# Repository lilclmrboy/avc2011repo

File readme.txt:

##########################################################################
# Readme.txt file for AVG2011 project

Download Acroname product sources and integrate the SVN repository. 
Aka, how do I get these files to just work with the download files. 
Launch a terminal session and get to it. 

1.) Move into a directory that you just downloaded the files from Acroname.
2.) Copy the files into your avc2011repo directory

$ cp -Rv acroname/ /Users/you/avc2011rep/source

That should be it. Get working!

##########################################################################
# TEAWare information
# Getting the Stem files ready for deployment to the Stem network

There is a make command to build the project settings for the stem network.

$ make dump

This should create a file to load all the TEAWare onto the Stem network. From the aConsole application:

brainstem> braindump avc2011_dump.dump
wtf

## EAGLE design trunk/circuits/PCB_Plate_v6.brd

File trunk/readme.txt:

# Readme.txt file for AVG2011 project

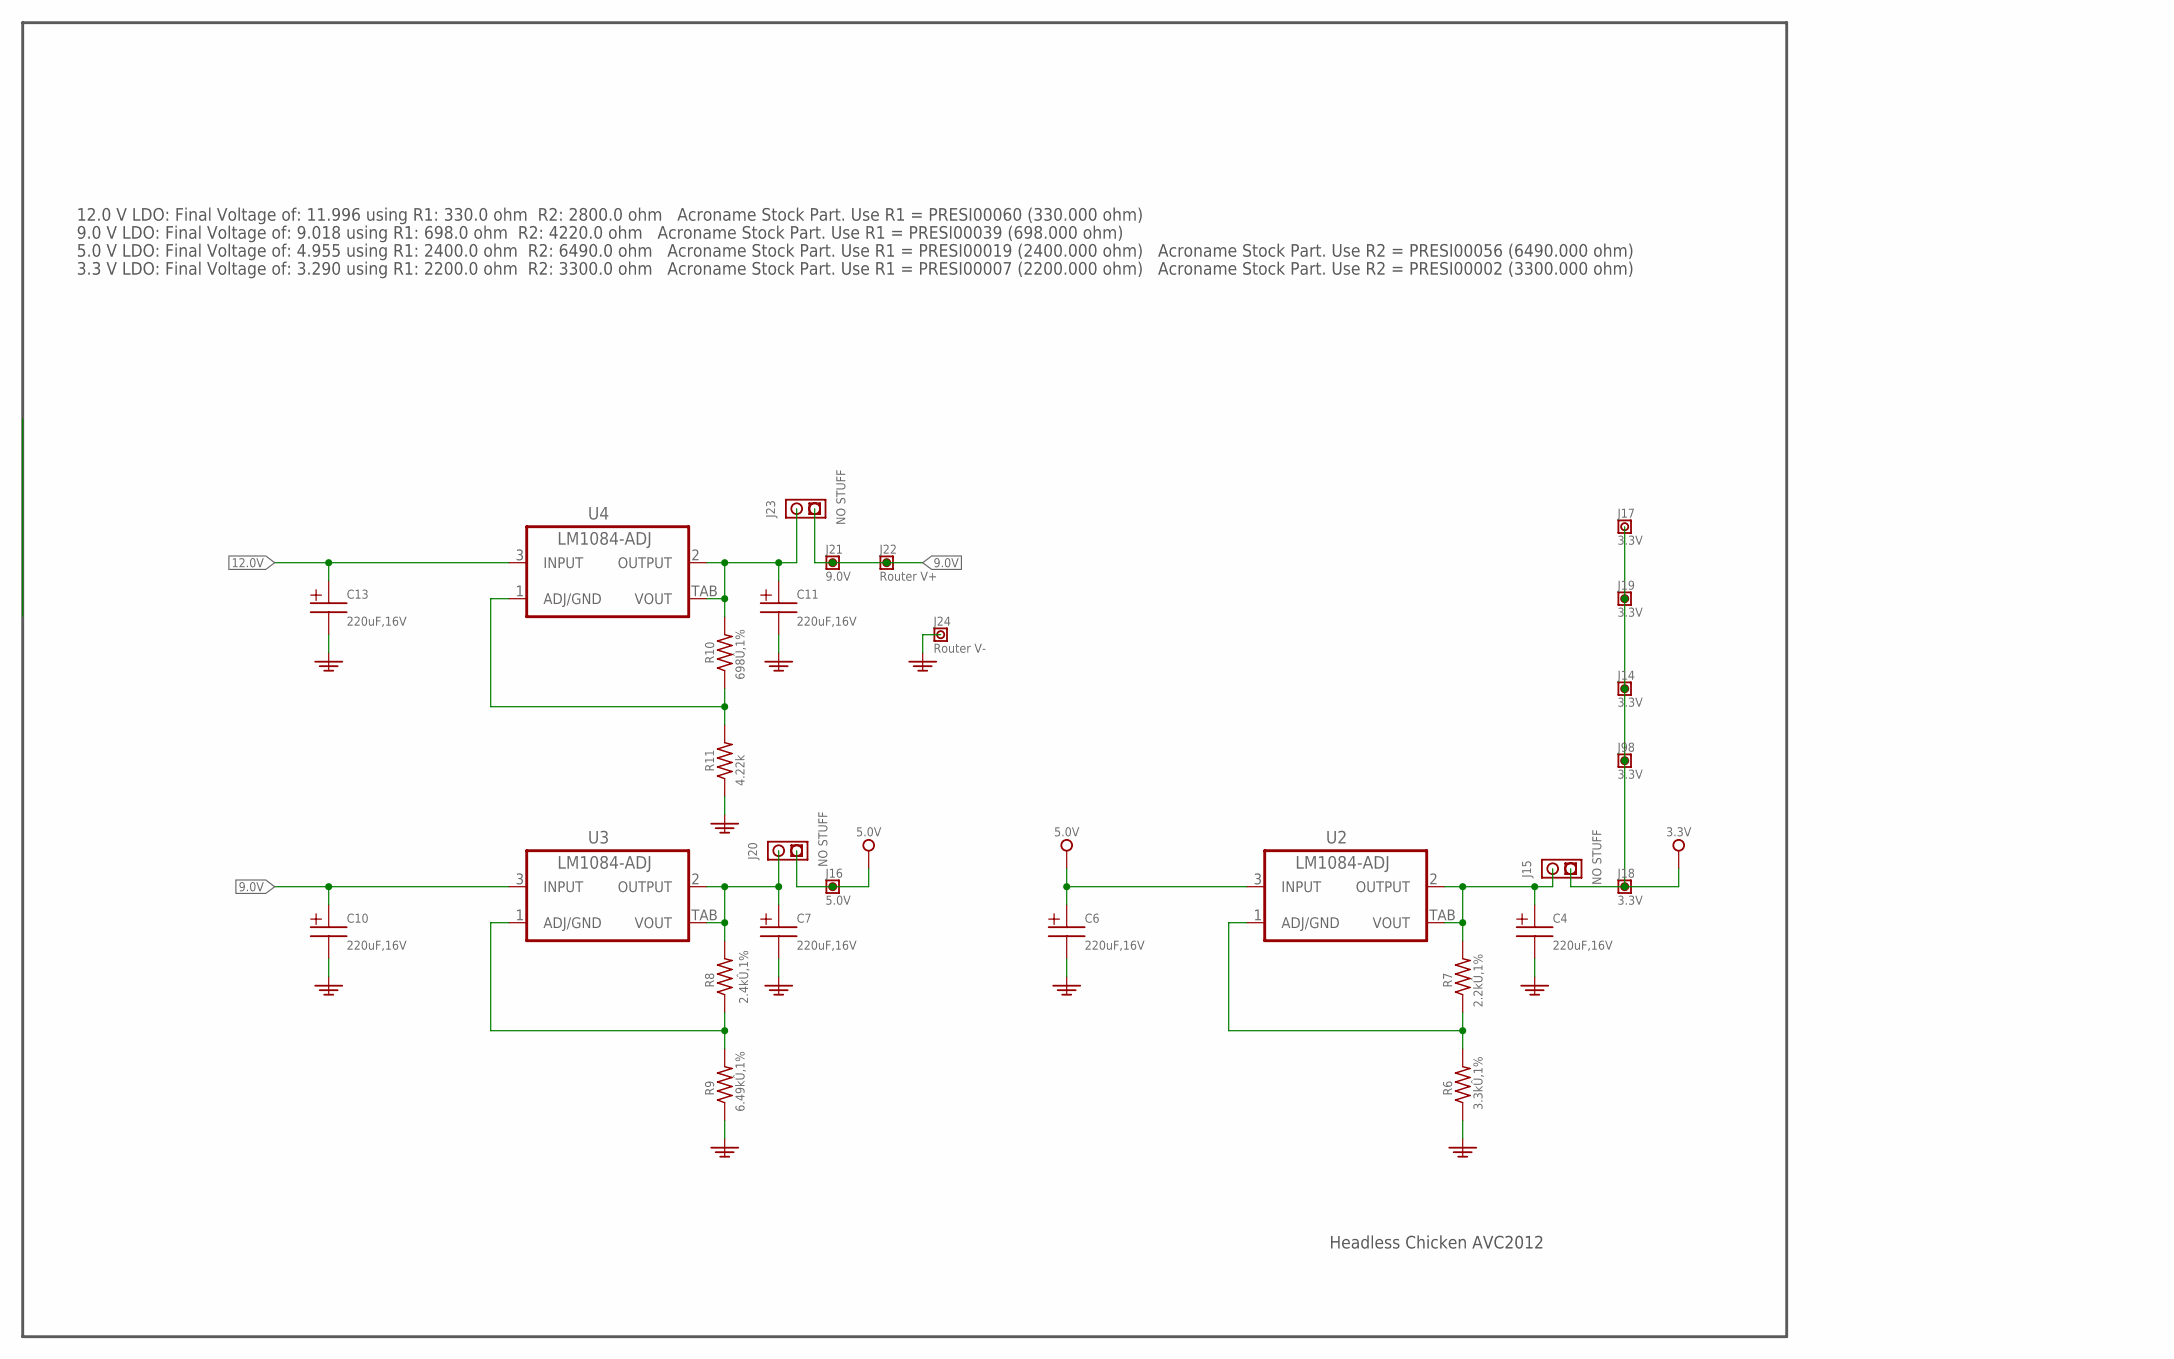
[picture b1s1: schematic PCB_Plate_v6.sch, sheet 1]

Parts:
C4, C6, C7, C10, C11, C13: T491D227K016ZT; SMC_D
J14, J17, J18, J19, J98: 3.3V; TSW1X1_VAL
J15, J20, J23: BOARD00012; TSW1X2
J16: 5.0V; TSW1X1_VAL
J21: 9.0V; TSW1X1_VAL
J22: Router V+; TSW1X1_VAL
J24: Router V-; TSW1X1_VAL
R6: on; R0603; PARTNUM ERJ-3GEYJ332V
R7: PRESI00007; R0603; PARTNUM ERJ-3GEYJ222V
R8: PRESI00019; R0603; PARTNUM ERJ-3EKF2431V
R9: on; R0402; PARTNUM ERJ-3EKF6491V
R10: PRESI00039; R0603; PARTNUM ERJ-3EKF6980V
R11: on; R0603
U2, U3, U4: LM1084IS-ADJ; TO263-3

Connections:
3V3: J14.P$1, J15.P$1, J17.P$1, J18.P$1, J19.P$1, J98.P$1; also elsewhere on the board
5V0: C6.+, J16.P$1, J20.P$1, U2.3 (INPUT); also elsewhere on the board
9.0V: C10.+, J21.P$1, J22.P$1, J23.P$1, U3.3 (INPUT)
12.0V: C13.+, U4.3 (INPUT); also elsewhere on the board
GND: C4.-, C6.-, C7.-, C10.-, C11.-, C13.-, J24.P$1, R6.1, R9.1, R11.1; also elsewhere on the board
unnamed: R10.1, R11.2, U4.1 (ADJ/GND)
unnamed: R8.1, R9.2, U3.1 (ADJ/GND)
unnamed: R6.2, R7.1, U2.1 (ADJ/GND)
unnamed: C7.+, J20.P$2, R8.2, U3.2 (OUTPUT), U3.TAB (VOUT)
unnamed: C11.+, J23.P$2, R10.2, U4.2 (OUTPUT), U4.TAB (VOUT)
unnamed: C4.+, J15.P$2, R7.2, U2.2 (OUTPUT), U2.TAB (VOUT)

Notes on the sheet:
Headless Chicken AVC2012
12.0 V LDO: Final Voltage of: 11.996 using R1: 330.0 ohm R2: 2800.0 ohm Acroname Stock Part. Use R1 = PRESI00060 (330.000 ohm)
9.0 V LDO: Final Voltage of: 9.018 using R1: 698.0 ohm R2: 4220.0 ohm Acroname Stock Part. Use R1 = PRESI00039 (698.000 ohm)
5.0 V LDO: Final Voltage of: 4.955 using R1: 2400.0 ohm R2: 6490.0 ohm Acroname Stock Part. Use R1 = PRESI00019 (2400.000 ohm) Acroname Stock Part. Use R2 = PRESI00056 (6490.000 ohm)
3.3 V LDO: Final Voltage of: 3.290 using R1: 2200.0 ohm R2: 3300.0 ohm Acroname Stock Part. Use R1 = PRESI00007 (2200.000 ohm) Acroname Stock Part. Use R2 = PRESI00002 (3300.000 ohm)

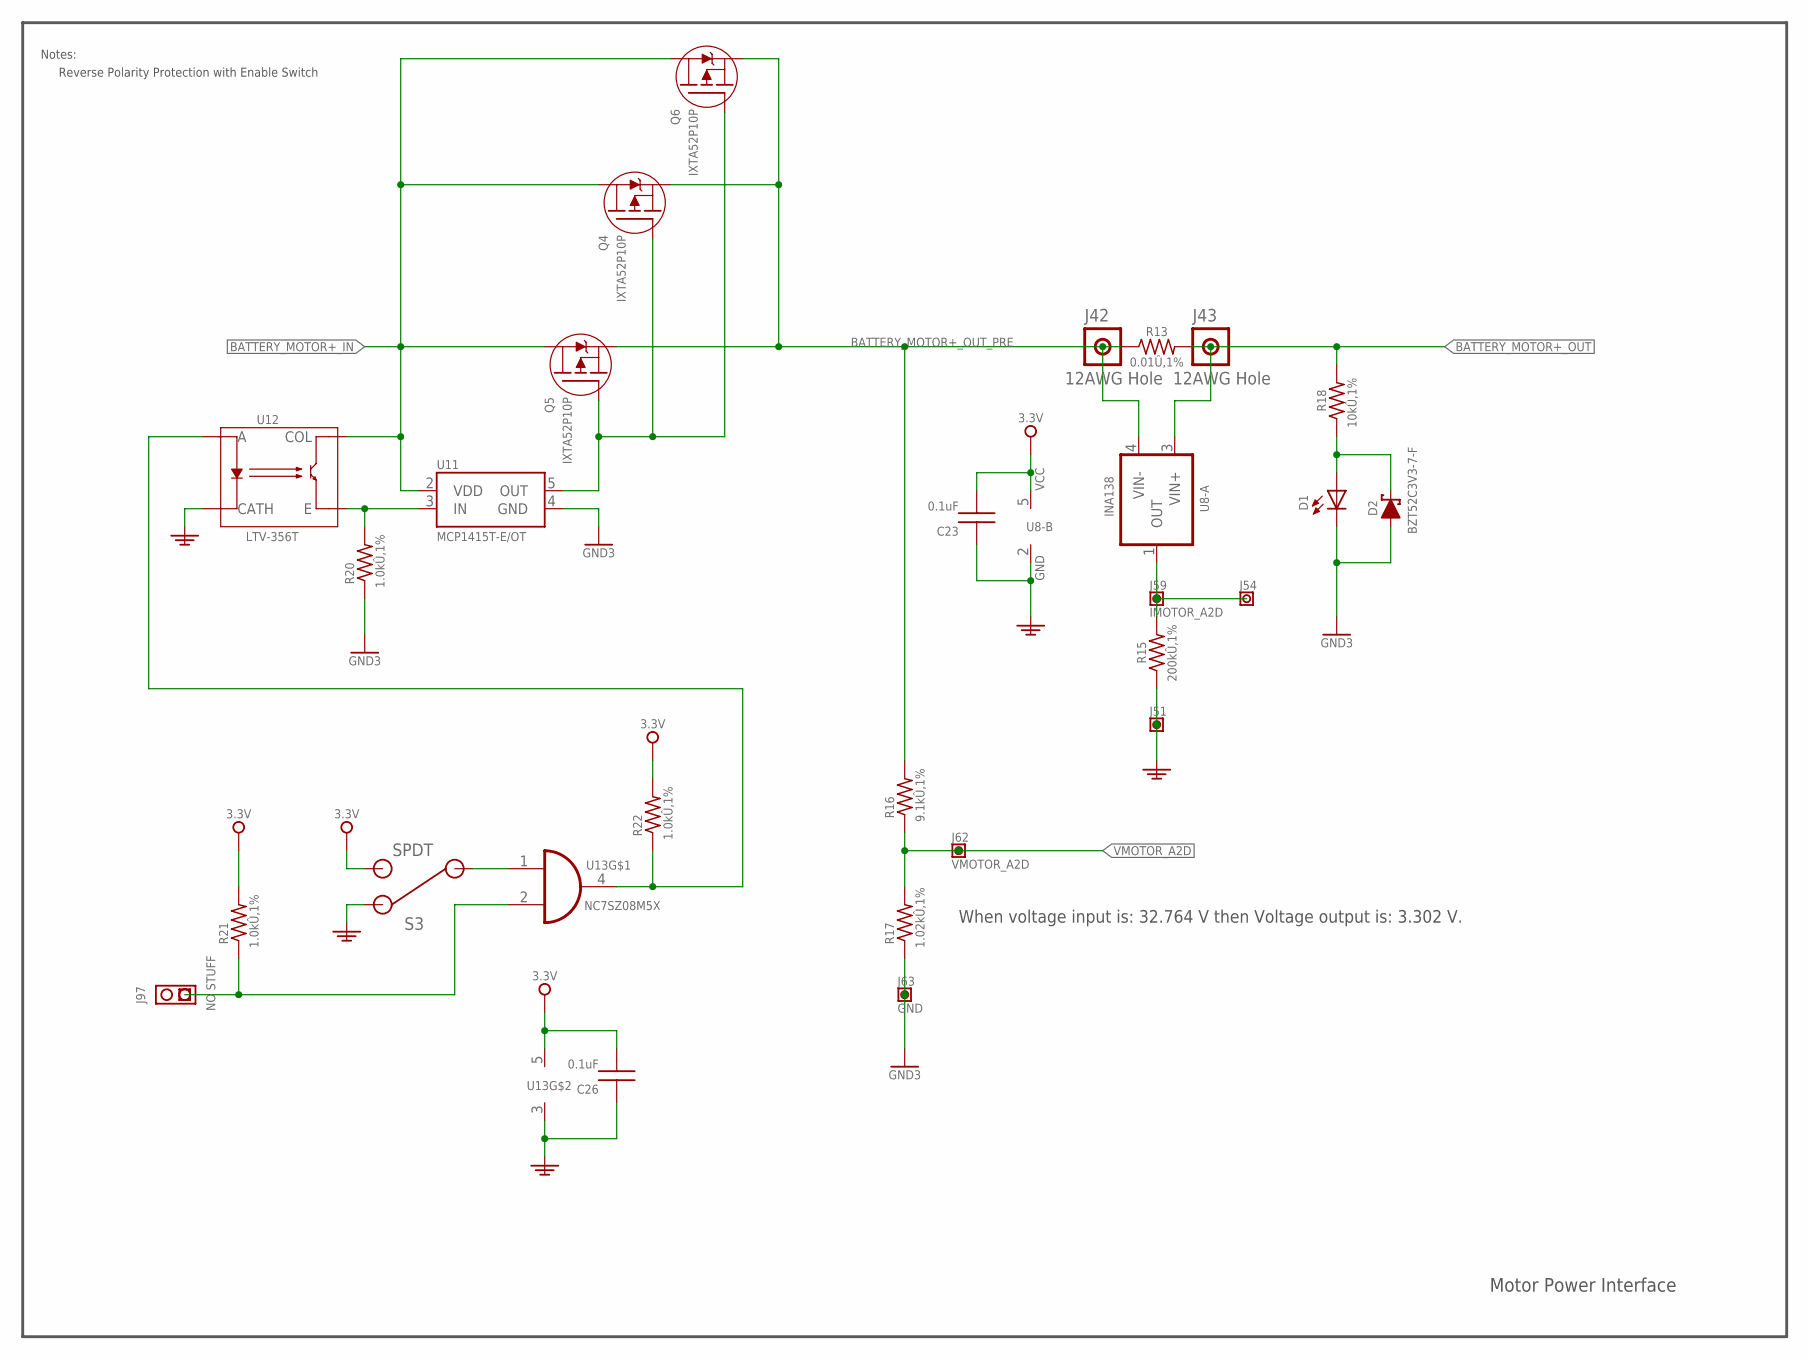
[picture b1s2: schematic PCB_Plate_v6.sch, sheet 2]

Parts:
C23: PCAPI00015; C0603
C26: PCAPI00015; C0603; PARTNUM ECJ-1VB1E104K
D1: PDIOD00001; CHIPLED_0805
D2: BZT52C3V3-7-F; SOD123
J42, J43: BOARD00008; TSW1X1_12AWG
J51, J54: BOARD00003WVALUE; TSW1X1_VAL
J59: IMOTOR_A2D; TSW1X1_VAL
J62: VMOTOR_A2D; TSW1X1_VAL
J63: GND; TSW1X1_VAL
J97: BOARD00012; TSW1X2
Q4, Q5, Q6: IXTA52P10P; D2PACK
R13: PRESI00041; R4527
R15: PRESI00018; R0603
R16: ERJ-2RKF9101X; R0402@1
R17: ERJ-2RKF1021X; R0402@1
R18: PRESI00005; R0603
R20, R21: PRESI00006; R0603; PARTNUM ERJ-3EKF1001V
R22: PRESI00006; R0603
S3: PMISC00005; SPDTRA
U8: PCHIP00026; SOT23-5
U11: MCP1416; SOT23-5; PARTNUM MCP1415T-E/OT
U12: LTV-356T; 4-SMD
U13: NC7SZ08M5X; SOT23-5

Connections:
3V3: C23.2, C26.2, R21.2, R22.2, S3.3 (2), U8.5 (VCC), U13.5 (VCC); also elsewhere on the board
BATTERY_MOTOR+_IN: Q4.D, Q5.D, Q6.D, U11.2 (VDD), U12.4 (COL); also elsewhere on the board
BATTERY_MOTOR+_OUT: J43.P$1, R13.2, R18.2, U8.3 (VIN+); also elsewhere on the board
BATTERY_MOTOR+_OUT_PRE: J42.P$1, Q4.S, Q5.S, Q6.S, R13.1, R16.2, U8.4 (VIN-)
GND: C23.1, C26.1, J51.P$1, R15.1, S3.1 (3), U8.2 (GND), U12.2 (CATH), U13.3 (GND); also elsewhere on the board
GND3: D1.C, D2.C (A), J63.P$1, R17.1, R20.1, U11.4 (GND); also elsewhere on the board
IMOTOR_A2D: J54.P$1, J59.P$1, R15.2, U8.1 (OUT)
unnamed: Q4.G, Q5.G, Q6.G, U11.5 (OUT)
unnamed: D1.A, D2.A (C), R18.1
unnamed: R22.1, U12.1 (A), U13.4 (O)
unnamed: S3.2 (1), U13.1 (I0)
unnamed: J97.P$1, R21.1, U13.2 (I1)
unnamed: R20.2, U11.3 (IN), U12.3 (E)
VMOTOR_A2D: J62.P$1, R16.1, R17.2

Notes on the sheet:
Reverse Polarity Protection with Enable Switch
Notes:
Motor Power Interface
When voltage input is: 32.764 V then Voltage output is: 3.302 V.

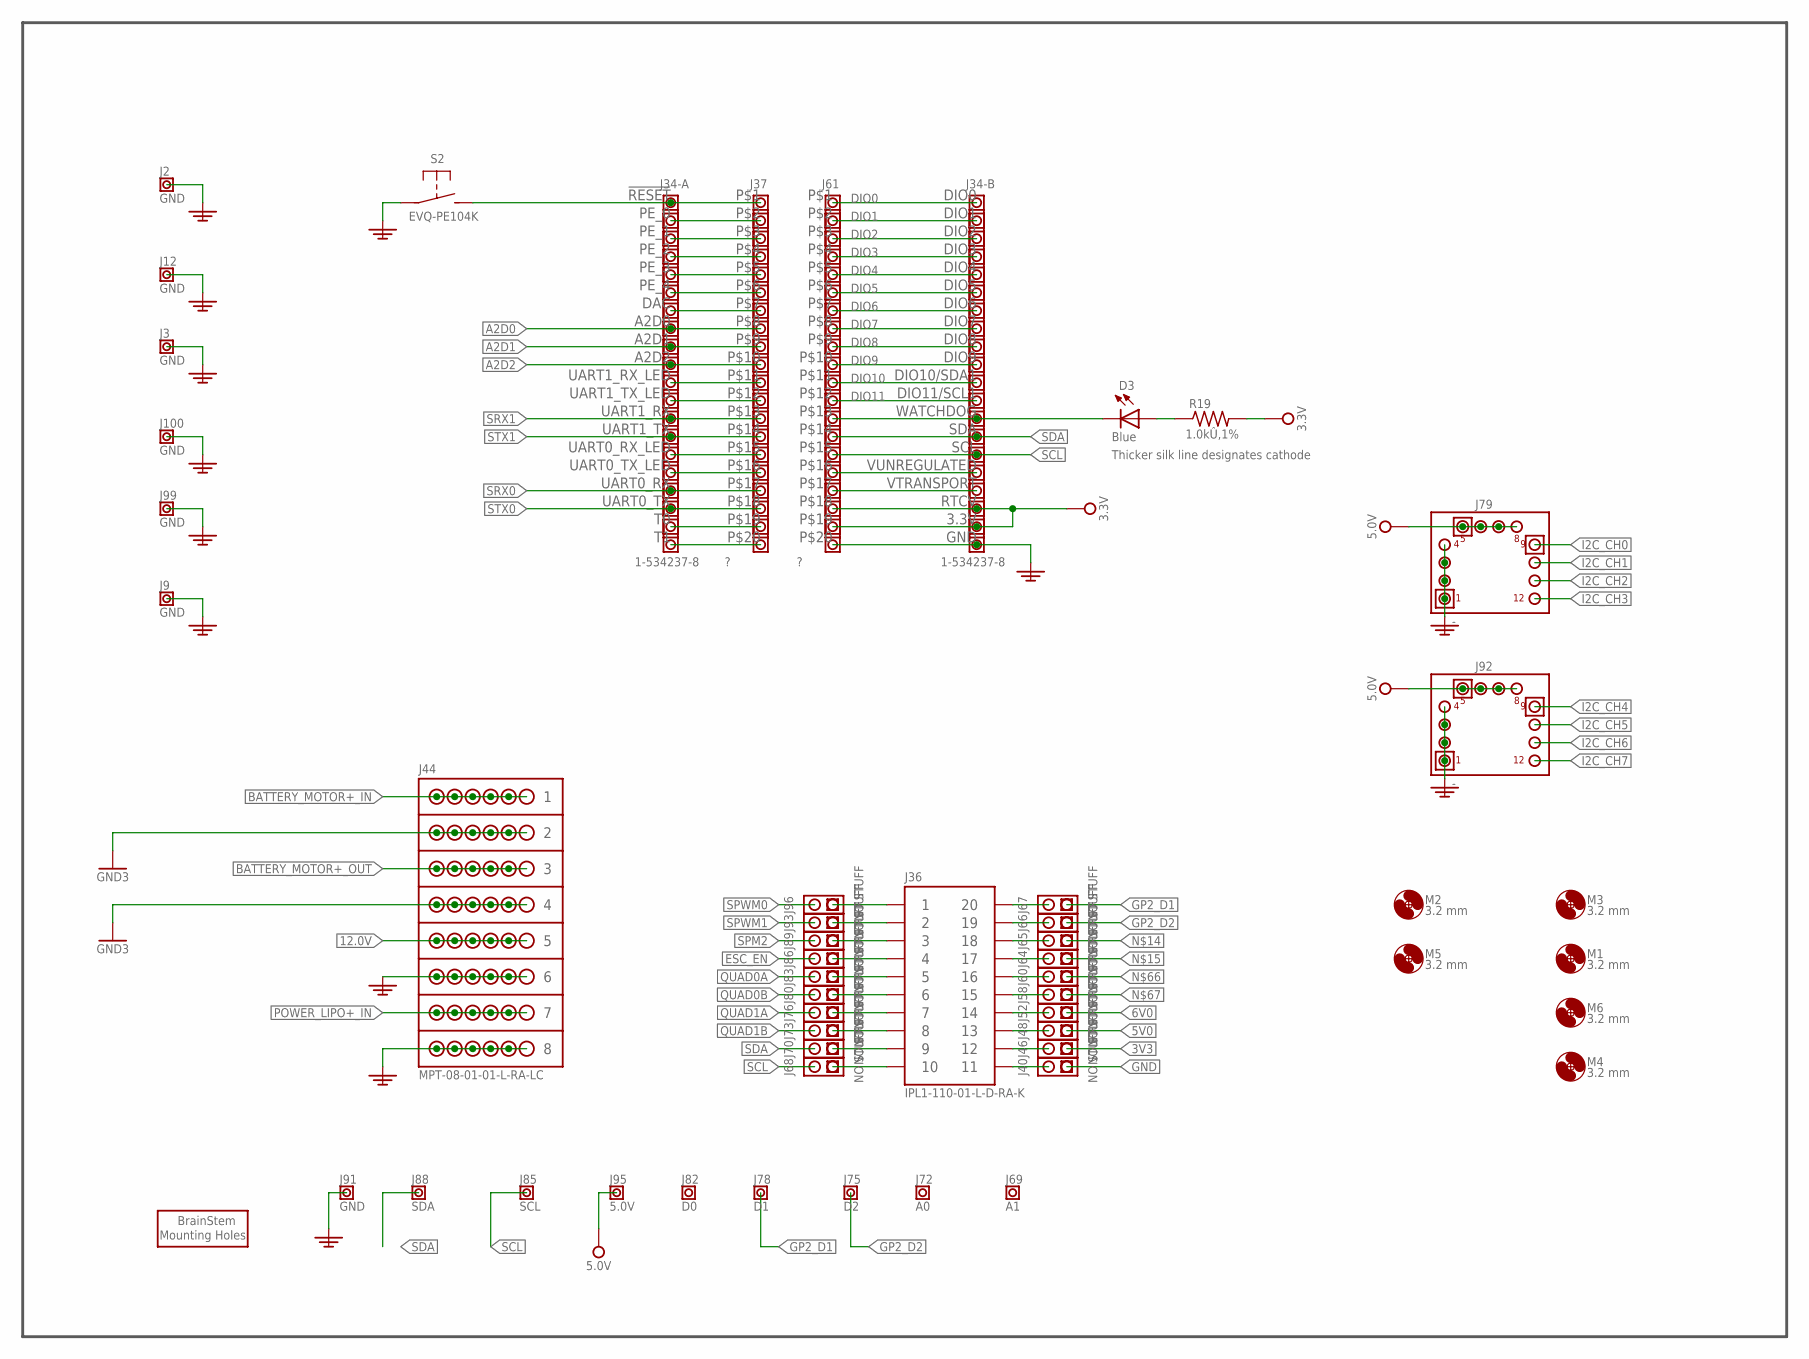
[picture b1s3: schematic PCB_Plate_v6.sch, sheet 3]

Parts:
D3: LTST-C171TBKT; CHIPLED_0805
J2, J3, J9, J12, J91, J99, J100: GND; TSW1X1_VAL
J34: BRAINSTEMSOCKET_FEMALE; BRAINSTEMSOCKET; PARTNUM 1-534237-8
J36: IPL1-1XX-02-XXX-DH-K-XX-MKT; IPL1-110-01-S-RA
J37, J61: TSW1X20
J40, J46, J48, J52, J58, J60, J64, J65, J66, J67, J68, J70, J73, J76, J80, J83, J86, J89, J93, J96: BOARD00012; TSW1X2
J44: MPT-08-01-01-L-RA-LC; MPT-08-XX-X-RA-XX
J69: A1; TSW1X1_VAL
J72: A0; TSW1X1_VAL
J75: D2; TSW1X1_VAL
J78: D1; TSW1X1_VAL
J79, J92: PCONN00012; TSW3X4RA
J82: D0; TSW1X1_VAL
J85: SCL; TSW1X1_VAL
J88: SDA; TSW1X1_VAL
J95: 5.0V; TSW1X1_VAL
M1, M2, M3, M4, M5, M6: MOUNT-HOLE3.2; 3,2
M7: BRAINSTEM_MOUNT
R19: PRESI00006; R0603
S2: EVQ-PE104K; SPST-NO

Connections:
3V3: J34.3.3V, J34.RTCV, J46.P$1, J61.P$18, J61.P$19, R19.2; also elsewhere on the board
5V0: J48.P$1, J79.P$5, J79.P$6, J79.P$7, J79.P$8, J92.P$5, J92.P$6, J92.P$7, J92.P$8, J95.P$1; also elsewhere on the board
6V0: J52.P$1
12.0V: J44.5@0 (5), J44.5@1 (5), J44.5@2 (5), J44.5@3 (5), J44.5@4 (5), J44.5@5 (5); also elsewhere on the board
!RESET: J34.!RESET, J37.P$1, S2.P$2 (S)
A2D0: J34.A2D0, J37.P$8; also elsewhere on the board
A2D1: J34.A2D1, J37.P$9; also elsewhere on the board
A2D2: J34.A2D2, J37.P$10; also elsewhere on the board
BATTERY_MOTOR+_IN: J44.1@0 (1), J44.1@1 (1), J44.1@2 (1), J44.1@3 (1), J44.1@4 (1), J44.1@5 (1); also elsewhere on the board
BATTERY_MOTOR+_OUT: J44.3@0 (3), J44.3@1 (3), J44.3@2 (3), J44.3@3 (3), J44.3@4 (3), J44.3@5 (3); also elsewhere on the board
DIO0: J34.DIO0, J61.P$1
DIO1: J34.DIO1, J61.P$2
DIO2: J34.DIO2, J61.P$3
DIO3: J34.DIO3, J61.P$4
DIO4: J34.DIO4, J61.P$5
DIO5: J34.DIO5, J61.P$6
DIO6: J34.DIO6, J61.P$7
DIO7: J34.DIO7, J61.P$8
DIO8: J34.DIO8, J61.P$9
DIO9: J34.DIO9, J61.P$10
DIO10: J34.DIO10/SDA1, J61.P$11
DIO11: J34.DIO11/SCL1, J61.P$12
ESC_EN: J86.P$2
GND: J2.P$1, J3.P$1, J9.P$1, J12.P$1, J34.GND, J40.P$1, J44.6@0 (6), J44.6@1 (6), J44.6@2 (6), J44.6@3 (6), J44.6@4 (6), J44.6@5 (6), J44.8@0 (1), J44.8@1 (1), J44.8@2 (1), J44.8@3 (1), J44.8@4 (1), J44.8@5 (8), J61.P$20, J79.P$1, J79.P$2, J79.P$3, J79.P$4, J91.P$1, J92.P$1, J92.P$2, J92.P$3, J92.P$4, J99.P$1, J100.P$1, S2.P$1; also elsewhere on the board
GND3: J44.2@0 (2), J44.2@1 (2), J44.2@2 (2), J44.2@3 (2), J44.2@4 (2), J44.2@5 (2), J44.4@0 (4), J44.4@1 (4), J44.4@2 (4), J44.4@3 (4), J44.4@4 (4), J44.4@5 (4); also elsewhere on the board
GP2_D1: J67.P$1, J78.P$1
GP2_D2: J66.P$1, J75.P$1
I2C_CH0: J79.P$9; also elsewhere on the board
I2C_CH1: J79.P$10; also elsewhere on the board
I2C_CH2: J79.P$11; also elsewhere on the board
I2C_CH3: J79.P$12; also elsewhere on the board
I2C_CH4: J92.P$9; also elsewhere on the board
I2C_CH5: J92.P$10; also elsewhere on the board
I2C_CH6: J92.P$11; also elsewhere on the board
I2C_CH7: J92.P$12; also elsewhere on the board
unnamed: D3.A, R19.1
unnamed: D3.C, J34.WATCHDOG, J61.P$13
unnamed: J34.PE_0, J37.P$2
unnamed: J34.PE_1, J37.P$3
unnamed: J34.PE_2, J37.P$4
unnamed: J34.PE_3, J37.P$5
unnamed: J34.PE_4, J37.P$6
unnamed: J34.DAC, J37.P$7
unnamed: J34.UART1_RX_LED, J37.P$11
unnamed: J34.UART1_TX_LED, J37.P$12
unnamed: J34.UART0_RX_LED, J37.P$15
unnamed: J34.UART0_TX_LED, J37.P$16
unnamed: J34.T0, J37.P$19
unnamed: J34.T1, J37.P$20
unnamed: J34.VTRANSPORT, J61.P$17
unnamed: J36.1, J96.P$1
unnamed: J36.2, J93.P$1
unnamed: J36.3, J89.P$1
unnamed: J36.4, J86.P$1
unnamed: J36.5, J83.P$1
unnamed: J36.6, J80.P$1
unnamed: J36.7, J76.P$1
unnamed: J36.8, J73.P$1
unnamed: J36.9, J70.P$1
unnamed: J36.10, J68.P$1
unnamed: J36.20, J67.P$2
unnamed: J36.19, J66.P$2
unnamed: J36.18, J65.P$2
unnamed: J36.17, J64.P$2
unnamed: J36.16, J60.P$2
unnamed: J36.15, J58.P$2
unnamed: J36.14, J52.P$2
unnamed: J36.13, J48.P$2
unnamed: J36.12, J46.P$2
unnamed: J36.11, J40.P$2
unnamed: J34.VUNREGULATED, J61.P$16
POWER_LIPO+_IN: J44.7@0 (7), J44.7@1 (7), J44.7@2 (7), J44.7@3 (7), J44.7@4 (7), J44.7@5 (7); also elsewhere on the board
QUAD0A: J83.P$2
QUAD0B: J80.P$2
QUAD1A: J76.P$2
QUAD1B: J73.P$2
SCL: J34.SCL, J61.P$15, J68.P$2, J85.P$1; also elsewhere on the board
SDA: J34.SDA, J61.P$14, J70.P$2, J88.P$1; also elsewhere on the board
SPM2: J89.P$2
SPWM0: J96.P$2
SPWM1: J93.P$2
SRX0: J34.UART0_RX, J37.P$17; also elsewhere on the board
SRX1: J34.UART1_RX, J37.P$13; also elsewhere on the board
STX0: J34.UART0_TX, J37.P$18; also elsewhere on the board
STX1: J34.UART1_TX, J37.P$14; also elsewhere on the board

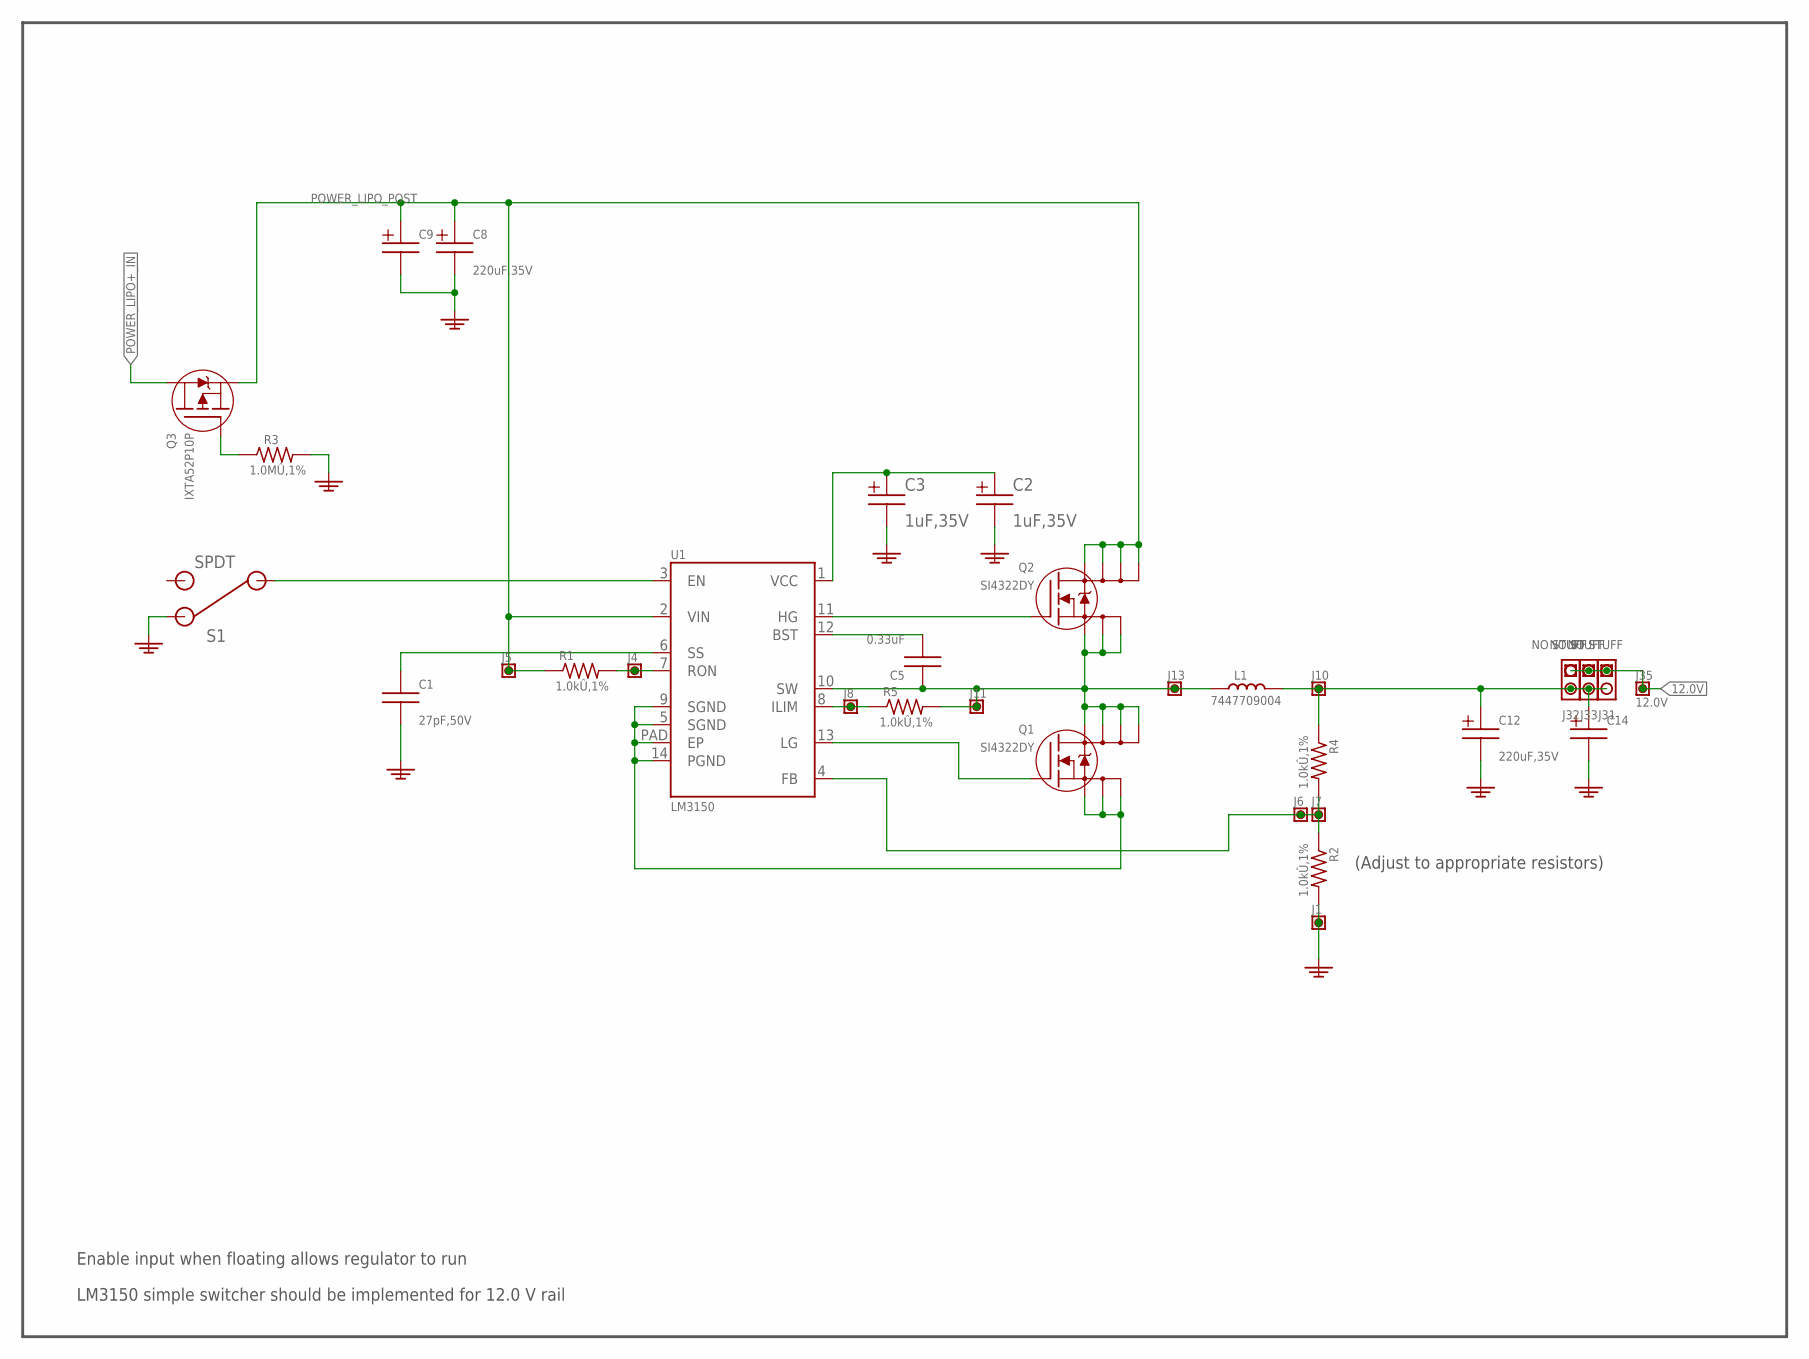
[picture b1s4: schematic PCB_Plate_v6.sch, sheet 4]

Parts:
C1: ECJ-1VC1H270J; C0603
C2, C3: T491B105K035AT; T491
C5: PCAPI00005; C0603
C8, C12: PCAPI00020; PANASONIC_G
C9, C14: CAP_POLARIZED; PANASONIC_NHG_A
J1, J4, J5, J6, J7, J8, J10, J11, J13: BOARD00003; TSW1X1
J31, J32, J33: BOARD00012; TSW1X2
J35: 12.0V; TSW1X1_VAL
L1: 7447709004
Q1, Q2: SI4322DY; SO-08
Q3: IXTA52P10P; D2PACK
R1, R2, R4, R5: PRESI00006; R0603
R3: ERJ-3EKF1004V; R0603
S1: PMISC00005; SPDTRA
U1: LM3150; TSSOP14EXP

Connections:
12.0V: J31.P$1, J32.P$1, J33.P$1, J35.P$1; also elsewhere on the board
GND: C1.2, C2.-, C3.-, C8.-, C9.-, C12.-, C14.-, J1.P$1, R2.2, R3.2, S1.1 (3); also elsewhere on the board
unnamed: S1.2 (1), U1.3 (EN)
unnamed: C12.+, C14.+, J10.P$1, J31.P$2, J32.P$2, J33.P$2, L1.2, R4.1
unnamed: C2.+, C3.+, U1.1 (VCC)
unnamed: Q1.1 (SA), Q1.2 (SB), Q1.3 (SC), U1.5 (SGND), U1.9 (SGND), U1.14 (PGND), U1.PAD (EP)
unnamed: Q1.4 (G), U1.13 (LG)
unnamed: Q2.4 (G), U1.11 (HG)
unnamed: Q3.G, R3.1
unnamed: J4.P$1, R1.2, U1.7 (RON)
unnamed: C5.1, J11.P$1, J13.P$1, L1.1, Q1.5 (DA), Q1.6 (DB), Q1.7 (DC), Q1.8 (DD), Q2.1 (SA), Q2.2 (SB), Q2.3 (SC), R5.2, U1.10 (SW)
unnamed: C5.2, U1.12 (BST)
unnamed: J6.P$1, J7.P$1, R2.1, R4.2, U1.4 (FB)
unnamed: J8.P$1, R5.1, U1.8 (ILIM)
unnamed: C1.1, U1.6 (SS)
POWER_LIPO+_IN: Q3.D; also elsewhere on the board
POWER_LIPO_POST: C8.+, C9.+, J5.P$1, Q2.5 (DA), Q2.6 (DB), Q2.7 (DC), Q2.8 (DD), Q3.S, R1.1, U1.2 (VIN)

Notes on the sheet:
LM3150 simple switcher should be implemented for 12.0 V rail
Enable input when floating allows regulator to run
(Adjust to appropriate resistors)

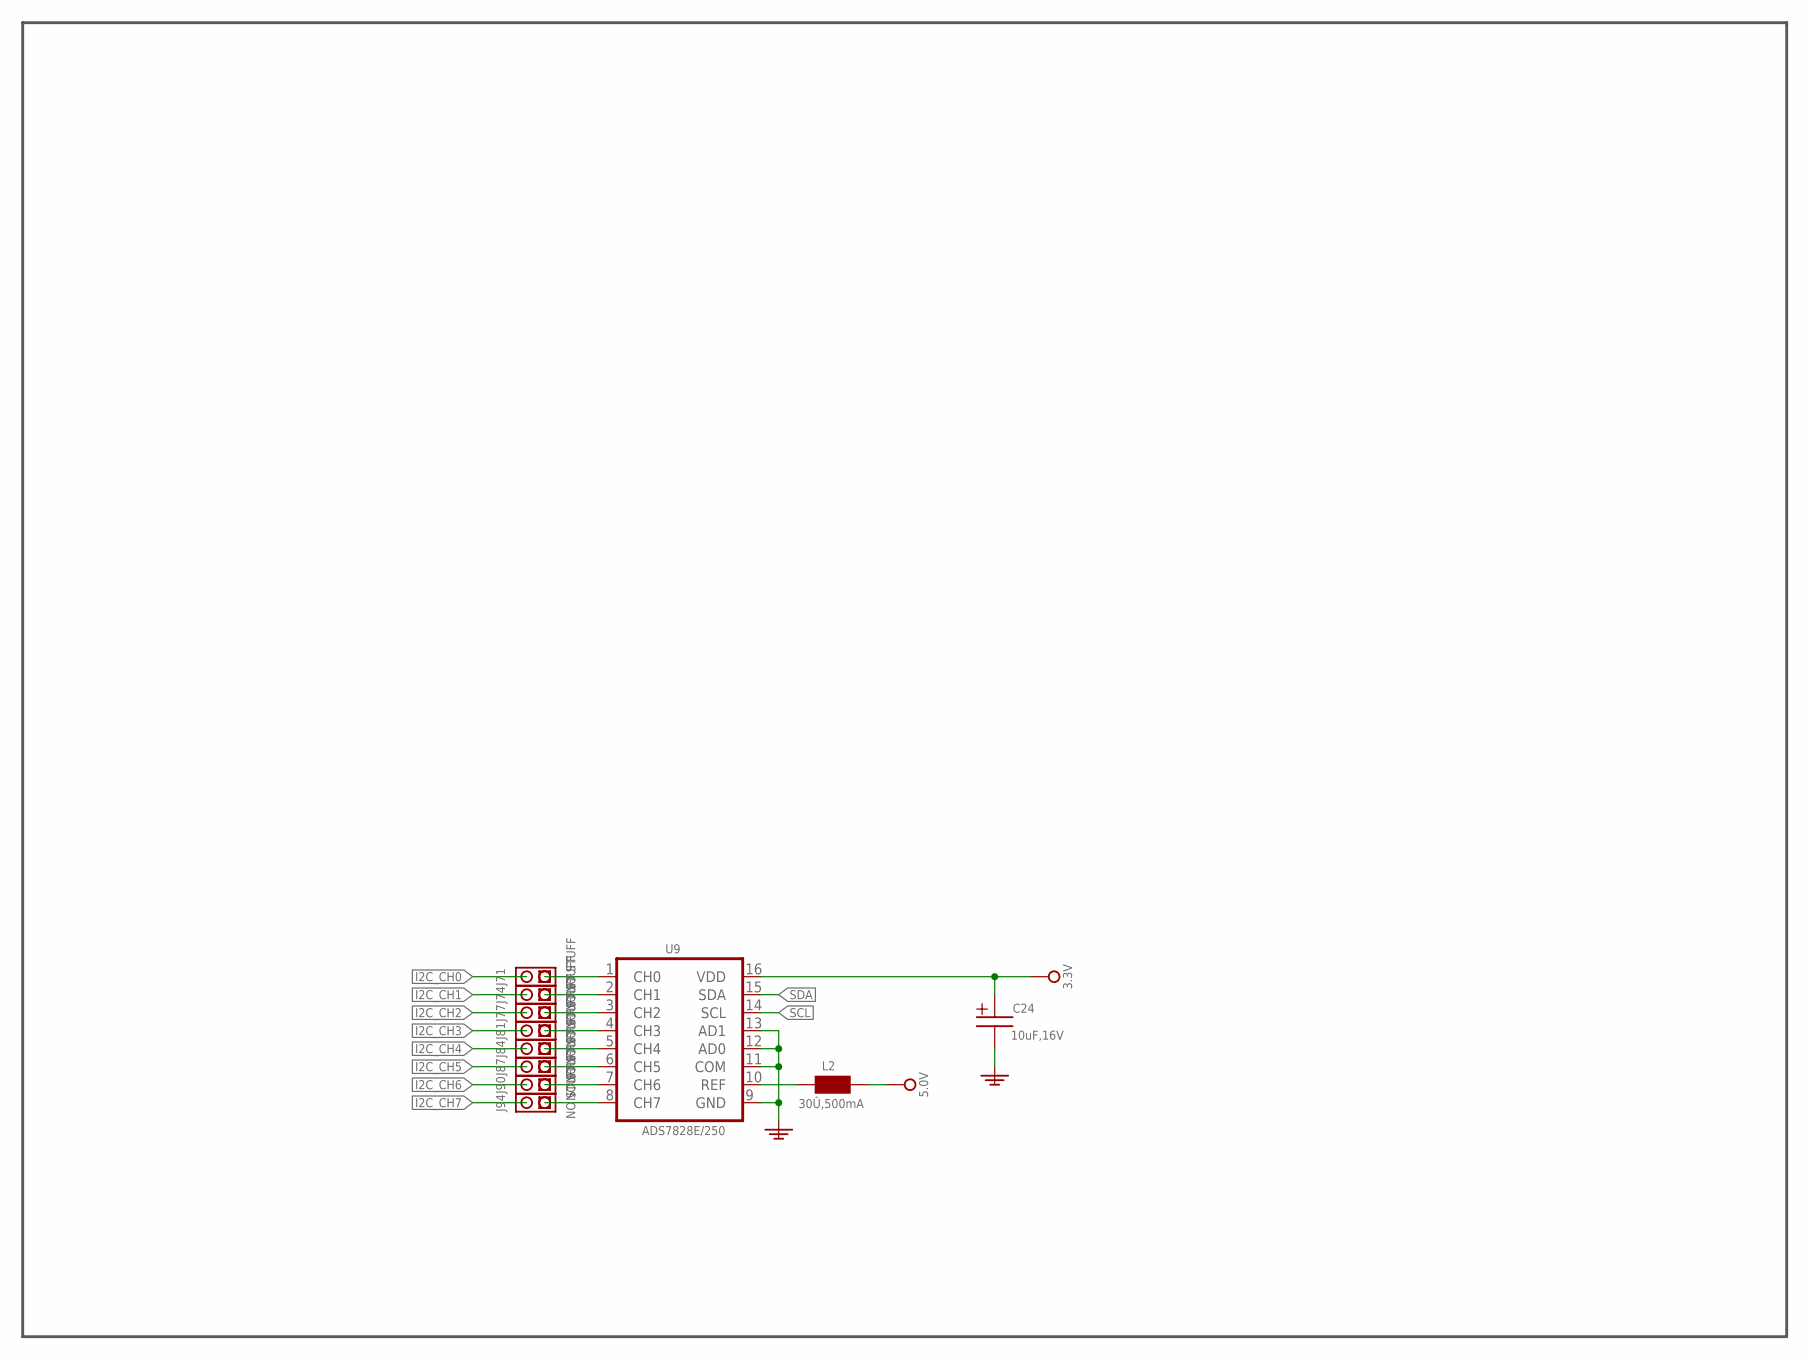
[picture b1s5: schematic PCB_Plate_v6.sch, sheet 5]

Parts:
C24: T491A106K010AT; SMC_A
J71, J74, J77, J81, J84, J87, J90, J94: BOARD00012; TSW1X2
L2: PMISC00013; L0402
U9: ADS7828E; TSSOP16

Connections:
3V3: C24.+, U9.16 (VDD); also elsewhere on the board
5V0: L2.2; also elsewhere on the board
GND: C24.-, U9.9 (GND), U9.11 (COM), U9.12 (AD0), U9.13 (AD1); also elsewhere on the board
I2C_CH0: J71.P$2; also elsewhere on the board
I2C_CH1: J74.P$2; also elsewhere on the board
I2C_CH2: J77.P$2; also elsewhere on the board
I2C_CH3: J81.P$2; also elsewhere on the board
I2C_CH4: J84.P$2; also elsewhere on the board
I2C_CH5: J87.P$2; also elsewhere on the board
I2C_CH6: J90.P$2; also elsewhere on the board
I2C_CH7: J94.P$2; also elsewhere on the board
unnamed: J71.P$1, U9.1 (CH0)
unnamed: L2.1, U9.10 (REF)
unnamed: J74.P$1, U9.2 (CH1)
unnamed: J77.P$1, U9.3 (CH2)
unnamed: J81.P$1, U9.4 (CH3)
unnamed: J84.P$1, U9.5 (CH4)
unnamed: J87.P$1, U9.6 (CH5)
unnamed: J90.P$1, U9.7 (CH6)
unnamed: J94.P$1, U9.8 (CH7)
SCL: U9.14 (SCL); also elsewhere on the board
SDA: U9.15 (SDA); also elsewhere on the board

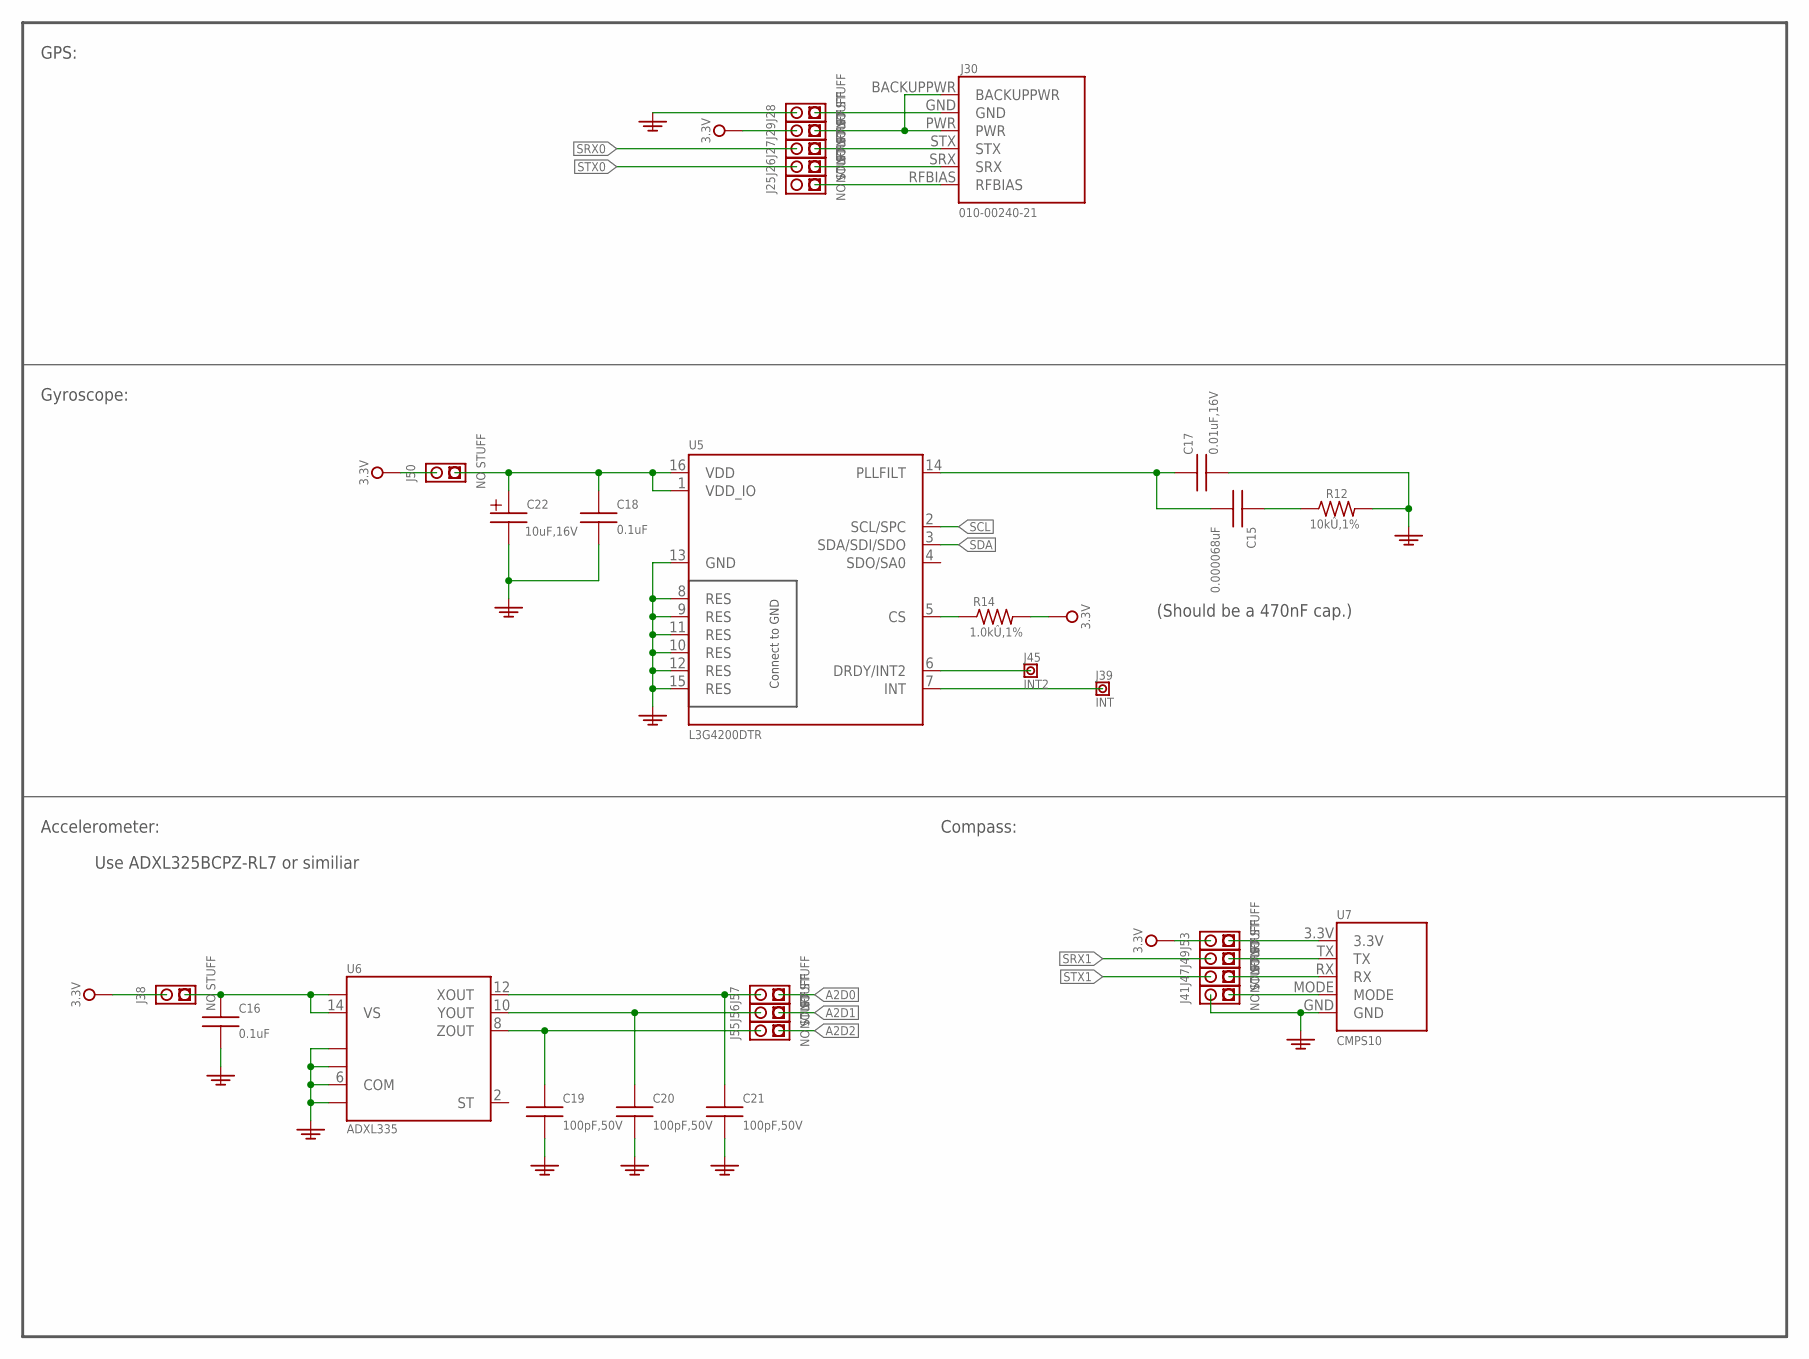
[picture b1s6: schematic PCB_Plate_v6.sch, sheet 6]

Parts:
C15: PCAPI00023; C0603
C16, C18: PCAPI00015; C0603
C17: PCAPI00007; C0603
C19, C20, C21: PCAPI00016; C0603
C22: T491A106K010AT; SMC_A
J25, J26, J27, J28, J29, J38, J41, J47, J49, J50, J53, J55, J56, J57: BOARD00012; TSW1X2
J30: GPS15X; GPS15
J39: INT; TSW1X1_VAL
J45: INT2; TSW1X1_VAL
R12: PRESI00005; R0603
R14: PRESI00006; R0603
U5: L3G4200DTR; LGA16
U6: ADXL335; LFCSP-16
U7: CMPS10

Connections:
3V3: J29.P$2, J38.P$2, J50.P$2, J53.P$2, R14.2; also elsewhere on the board
A2D0: J57.P$1; also elsewhere on the board
A2D1: J56.P$1; also elsewhere on the board
A2D2: J55.P$1; also elsewhere on the board
GND: C16.2, C17.2, C18.2, C19.2, C20.2, C21.2, C22.-, J28.P$2, J41.P$2, R12.2, U5.8 (RES), U5.9 (RES), U5.10 (RES), U5.11 (RES), U5.12 (RES), U5.13 (GND), U5.15 (RES), U6.3 (COM), U6.5 (COM), U6.6 (COM), U6.7 (COM), U7.GND; also elsewhere on the board
unnamed: J41.P$1, U7.MODE
unnamed: C18.1, C22.+, J50.P$1, U5.1 (VDD_IO), U5.16 (VDD)
unnamed: R14.1, U5.5 (CS)
unnamed: J29.P$1, J30.BACKUPPWR, J30.PWR
unnamed: J28.P$1, J30.GND
unnamed: J27.P$1, J30.STX
unnamed: J26.P$1, J30.SRX
unnamed: J25.P$1, J30.RFBIAS
unnamed: C15.2, C17.1, U5.14 (PLLFILT)
unnamed: C15.1, R12.1
unnamed: J39.P$1, U5.7 (INT)
unnamed: J45.P$1, U5.6 (DRDY/INT2)
unnamed: J53.P$1, U7.3.3V
unnamed: J49.P$1, U7.TX
unnamed: J47.P$1, U7.RX
unnamed: C16.1, J38.P$1, U6.14 (VS), U6.15 (VS)
unnamed: C19.1, J55.P$2, U6.8 (ZOUT)
unnamed: C20.1, J56.P$2, U6.10 (YOUT)
unnamed: C21.1, J57.P$2, U6.12 (XOUT)
SCL: U5.2 (SCL/SPC); also elsewhere on the board
SDA: U5.3 (SDA/SDI/SDO); also elsewhere on the board
SRX0: J27.P$2; also elsewhere on the board
SRX1: J49.P$2; also elsewhere on the board
STX0: J26.P$2; also elsewhere on the board
STX1: J47.P$2; also elsewhere on the board

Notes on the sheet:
Gyroscope:
GPS:
Accelerometer:
(Should be a 470nF cap.)
Use ADXL325BCPZ-RL7 or similiar
Compass:
